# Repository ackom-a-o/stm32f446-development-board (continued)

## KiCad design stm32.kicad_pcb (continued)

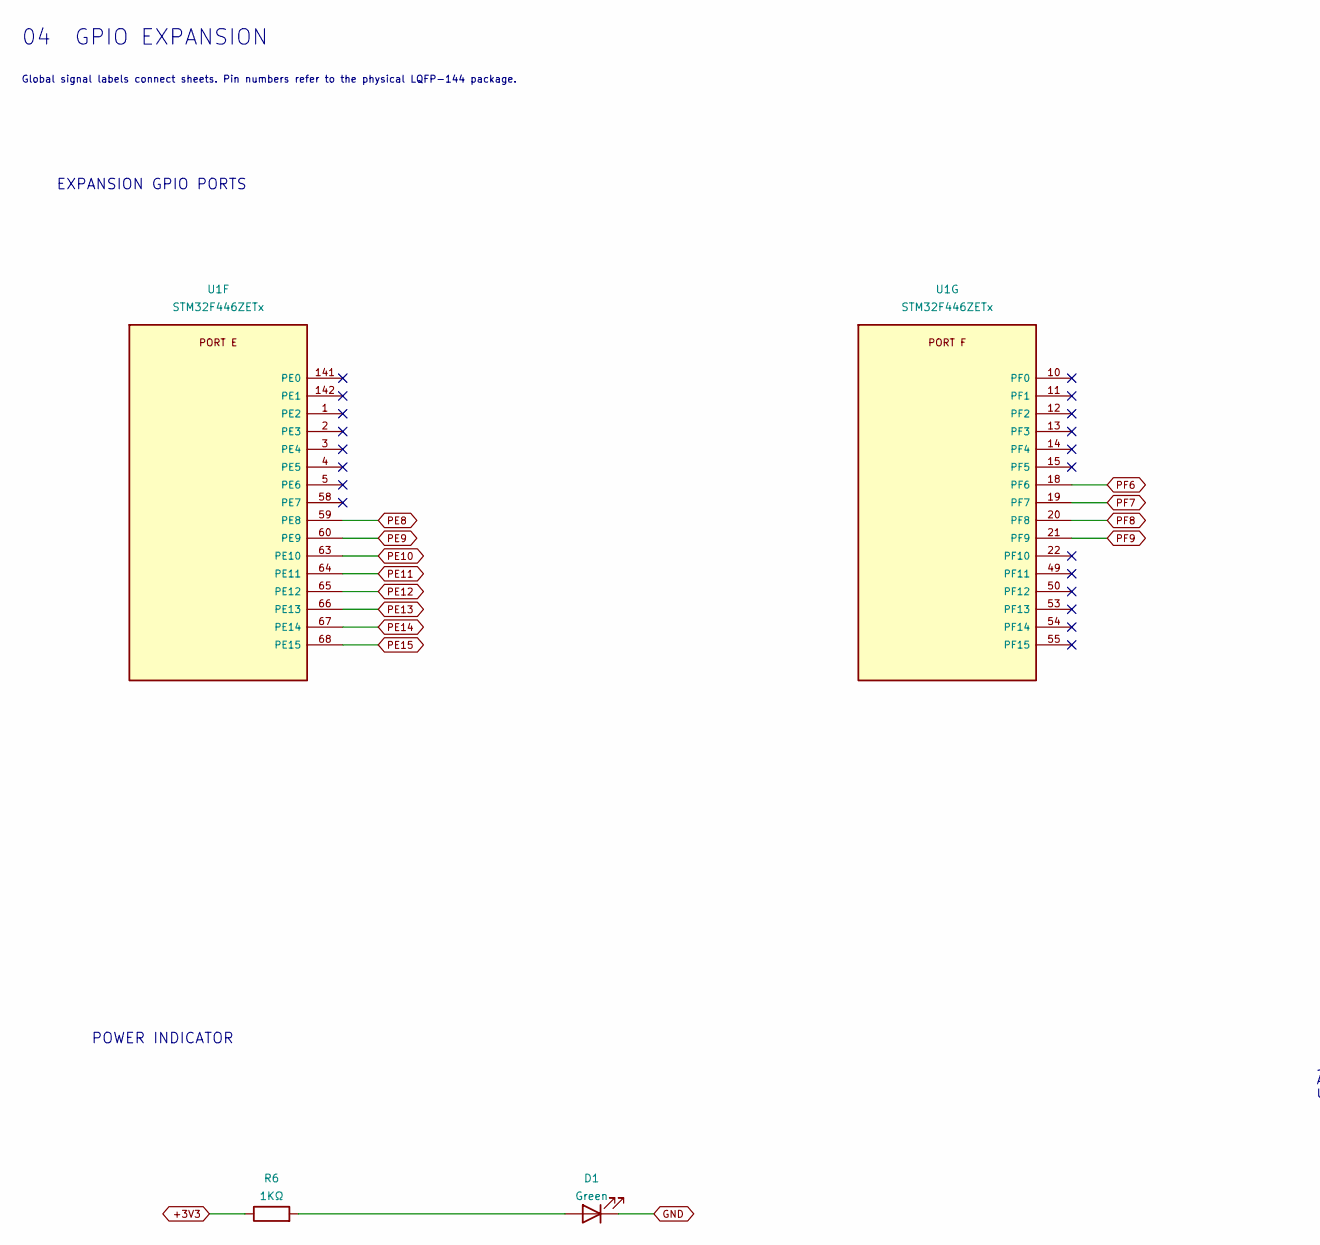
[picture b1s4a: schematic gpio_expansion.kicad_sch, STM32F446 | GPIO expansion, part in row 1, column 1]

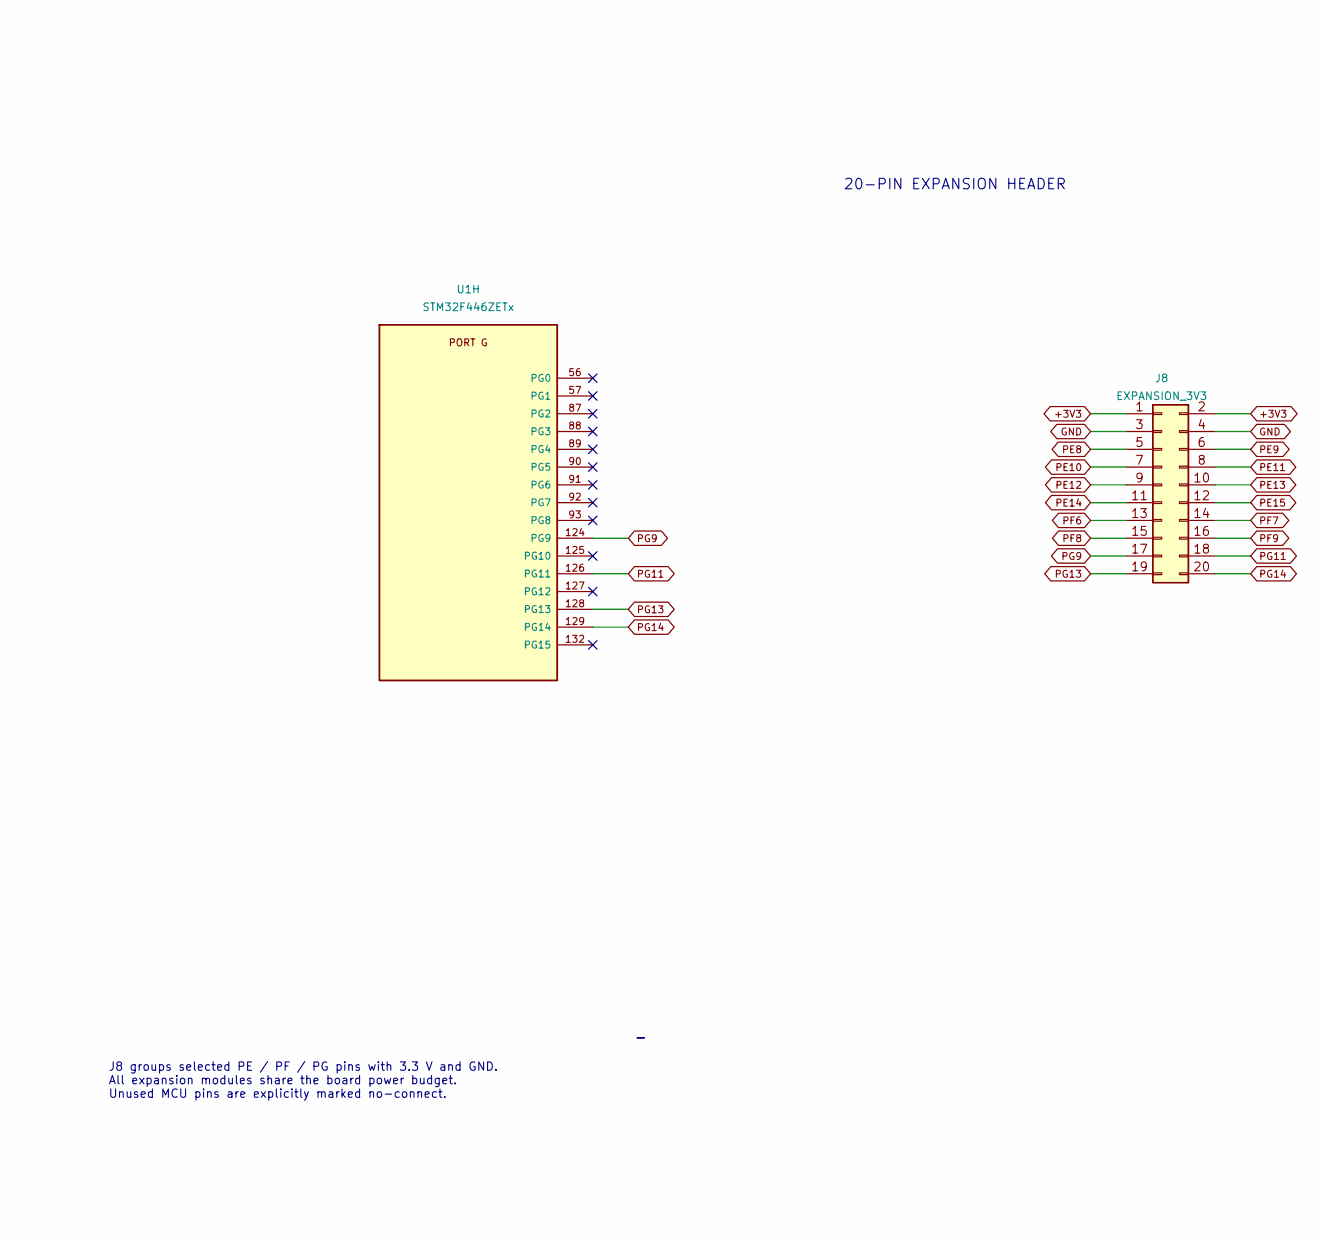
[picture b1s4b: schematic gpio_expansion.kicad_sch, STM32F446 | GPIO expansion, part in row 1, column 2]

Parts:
D1: Green; LED_0805_2012Metric; Manufacturer Part Number KT-0805G; LCSC Part Number C2297
J8: EXPANSION_3V3; PinHeader_2x10_P2.54mm_Vertical; Manufacturer Part Number PZ254V-12-20P; LCSC Part Number C492427
R6: 1KΩ; R_0805_2012Metric; Manufacturer Part Number 0805W8F1001T5E; LCSC Part Number C17513
U1: STM32F446ZETx; LQFP-144_20x20mm_P0.5mm; Manufacturer Part Number STM32F446ZET6; LCSC Part Number C1337227

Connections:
+3V3: J8.1, J8.2, R6.1; also elsewhere on the board
GND: D1.1 (K), J8.3, J8.4; also elsewhere on the board
unnamed: D1.2 (A), R6.2
PE8: J8.5, U1.59 (PE8)
PE9: J8.6, U1.60 (PE9)
PE10: J8.7, U1.63 (PE10)
PE11: J8.8, U1.64 (PE11)
PE12: J8.9, U1.65 (PE12)
PE13: J8.10, U1.66 (PE13)
PE14: J8.11, U1.67 (PE14)
PE15: J8.12, U1.68 (PE15)
PF6: J8.13, U1.18 (PF6)
PF7: J8.14, U1.19 (PF7)
PF8: J8.15, U1.20 (PF8)
PF9: J8.16, U1.21 (PF9)
PG9: J8.17, U1.124 (PG9)
PG11: J8.18, U1.126 (PG11)
PG13: J8.19, U1.128 (PG13)
PG14: J8.20, U1.129 (PG14)

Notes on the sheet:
20-PIN EXPANSION HEADER
POWER INDICATOR
Global signal labels connect sheets. Pin numbers refer to the physical LQFP-144 package.
04 GPIO EXPANSION
EXPANSION GPIO PORTS
J8 groups selected PE / PF / PG pins with 3.3 V and GND. All expansion modules share the board power budget. Unused MCU pins are explicitly marked no-connect.

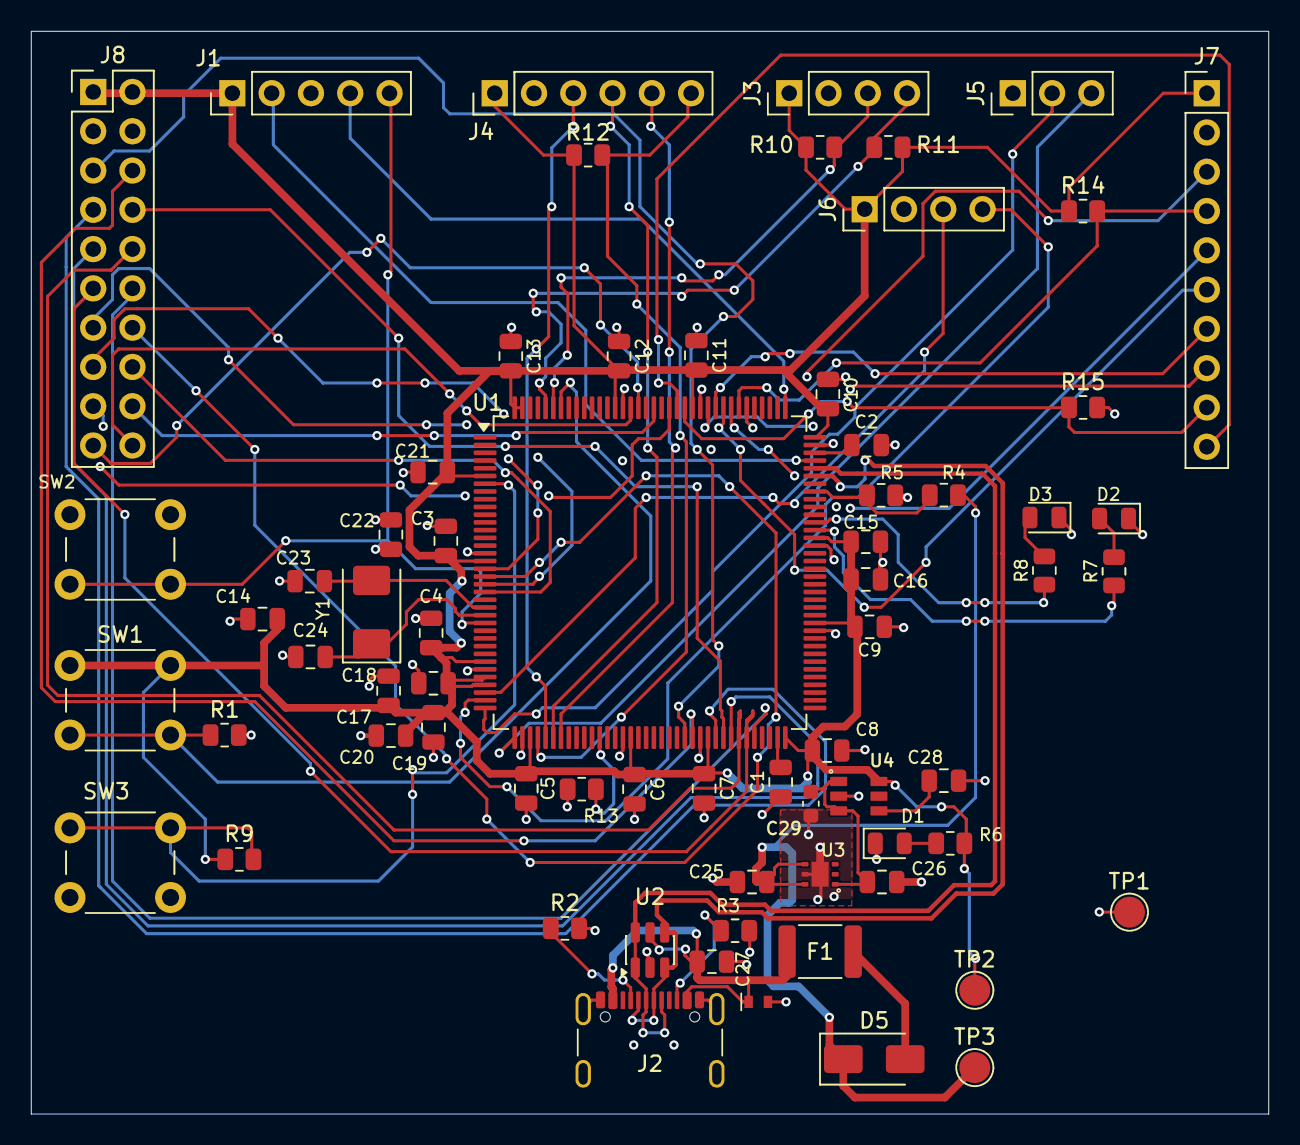
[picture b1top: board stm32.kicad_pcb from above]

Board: 4 copper layers, 80.0 x 70.0 mm, 69 parts (0 on the bottom side), 61 nets.

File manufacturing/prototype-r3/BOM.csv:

Comment,Designator,Footprint,LCSC Part #
2.2uF,C1,Capacitor_SMD:C_0805_2012Metric,C16195008
2.2uF,C2,Capacitor_SMD:C_0805_2012Metric,C16195008
100nF,C3,Capacitor_SMD:C_0805_2012Metric,C49678
100nF,C4,Capacitor_SMD:C_0805_2012Metric,C49678
100nF,C5,Capacitor_SMD:C_0805_2012Metric,C49678
100nF,C6,Capacitor_SMD:C_0805_2012Metric,C49678
100nF,C7,Capacitor_SMD:C_0805_2012Metric,C49678
100nF,C8,Capacitor_SMD:C_0805_2012Metric,C49678
100nF,C9,Capacitor_SMD:C_0805_2012Metric,C49678
100nF,C10,Capacitor_SMD:C_0805_2012Metric,C49678
100nF,C11,Capacitor_SMD:C_0805_2012Metric,C49678
100nF,C12,Capacitor_SMD:C_0805_2012Metric,C49678
100nF,C13,Capacitor_SMD:C_0805_2012Metric,C49678
4.7uF,C14,Capacitor_SMD:C_0805_2012Metric,C1779
100nF,C15,Capacitor_SMD:C_0805_2012Metric,C49678
1µF,C16,Capacitor_SMD:C_0805_2012Metric,C28323
100nF,C17,Capacitor_SMD:C_0805_2012Metric,C49678
1µF,C18,Capacitor_SMD:C_0805_2012Metric,C28323
100nF,C19,Capacitor_SMD:C_0805_2012Metric,C49678
1µF,C20,Capacitor_SMD:C_0805_2012Metric,C28323
100nF,C21,Capacitor_SMD:C_0805_2012Metric,C49678
100nF,C22,Capacitor_SMD:C_0805_2012Metric,C49678
22pF C0G,C23,Capacitor_SMD:C_0805_2012Metric,C1804
22pF C0G,C24,Capacitor_SMD:C_0805_2012Metric,C1804
2.2uF25VX7R,C25,Capacitor_SMD:C_0805_2012Metric,C16195008
2.2uF 25V X7R,C26,Capacitor_SMD:C_0805_2012Metric,C16195008
100nF,C27,Capacitor_SMD:C_0805_2012Metric,C49678
4.7nF,C28,Capacitor_SMD:C_0805_2012Metric,C107153
1µF,C29,Capacitor_SMD:C_0603_1608Metric,C29936
Green,D1,LED_SMD:LED_0805_2012Metric,C2297
LED1,D2,LED_SMD:LED_0805_2012Metric,C2295
LED2,D3,LED_SMD:LED_0805_2012Metric,C2295
ESDA7P120-1U1M,D4,STM32_Custom:ESDA7P60-1U1M,C2969802
SS14,D5,Diode_SMD:D_SMA,C2480
500mA,F1,Fuse:Fuse_1812_4532Metric,C17313
SWD,J1,Connector_PinHeader_2.54mm:PinHeader_1x05_P2.54mm_Vertical,C55629812
USB_C_Receptacle_USB2.0_16P,J2,STM32_Custom:USB_C_Receptacle_USB4105_JLC,C5184243
I²C1,J3,Connector_PinHeader_2.54mm:PinHeader_1x04_P2.54mm_Vertical,C492403
SPI1,J4,Connector_PinHeader_2.54mm:PinHeader_1x06_P2.54mm_Vertical,C5142852
UART2_3V3,J5,Connector_PinHeader_2.54mm:PinHeader_1x03_P2.54mm_Vertical,C18213718
ANALOG_3V3,J6,Connector_PinHeader_2.54mm:PinHeader_1x04_P2.54mm_Vertical,C492403
GPIO_D,J7,Connector_PinHeader_2.54mm:PinHeader_1x10_P2.54mm_Vertical,C492409
EXPANSION_3V3,J8,Connector_PinHeader_2.54mm:PinHeader_2x10_P2.54mm_Vertical,C492427
10kΩ,R1,Resistor_SMD:R_0805_2012Metric,C17414
5.1kΩ 1%,R2,Resistor_SMD:R_0805_2012Metric,C27834
5.1kΩ 1%,R3,Resistor_SMD:R_0805_2012Metric,C27834
"33kΩ,1%",R4,Resistor_SMD:R_0805_2012Metric,C17633
"82kΩ,1%",R5,Resistor_SMD:R_0805_2012Metric,C17840
1KΩ,R6,Resistor_SMD:R_0805_2012Metric,C17513
1KΩ,R7,Resistor_SMD:R_0805_2012Metric,C17513
1KΩ,R8,Resistor_SMD:R_0805_2012Metric,C17513
10kΩ,R9,Resistor_SMD:R_0805_2012Metric,C17414
4.7kΩ,R10,Resistor_SMD:R_0805_2012Metric,C17673
4.7kΩ,R11,Resistor_SMD:R_0805_2012Metric,C17673
10kΩ,R12,Resistor_SMD:R_0805_2012Metric,C17414
10kΩ,R13,Resistor_SMD:R_0805_2012Metric,C17414
10kΩ,R14,Resistor_SMD:R_0805_2012Metric,C17414
10kΩ,R15,Resistor_SMD:R_0805_2012Metric,C17414
SW_Push_Open,SW1,Button_Switch_THT:SW_PUSH_6mm_H4.3mm,C93157
SW_Push_Open,SW2,Button_Switch_THT:SW_PUSH_6mm_H4.3mm,C93157
SW_Push_Open,SW3,Button_Switch_THT:SW_PUSH_6mm_H4.3mm,C93157
STM32F446ZETx,U1,Package_QFP:LQFP-144_20x20mm_P0.5mm,C1337227
USBLC6-2SC6,U2,Package_TO_SOT_SMD:SOT-23-6,C7519
TPS7A2533DRVR,U3,STM32_Custom:TPS7A25_DRV0006A,C2867820
TPS22918DBVR,U4,STM32_Custom:TPS22918_DBV0006A,C131941
8MHz,Y1,Crystal:Crystal_SMD_Abracon_ABM3-2Pin_5.0x3.2mm,C2450458
